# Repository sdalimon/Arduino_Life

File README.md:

# Arduino_Life
A little Arduino compatible LED art project

It consists of a two board stack.  
The lower board has an ATMega328 loaded with the Arduino bootloader.  It also has the row drivers for the LED array.
The upper board is an 8x8 array of LEDs in a standard row/column arrangement.

This was called Arduino Life because I planned to do Game of Life on it, but found a nicer looking pattern that doesn't need to worry about geting stuck.

The software is in the LED_Worm which implements a dot bouncing around the LEDs toggleing the current LED.  It randomly turns to give a less repeatitive pattern.  The software is written using the Arduino IDE.  

To program, use a USB to TTL (or other TTL UART) interface.  Press the reset button after clicking Program in the Arduino IDE (or install the chip in an Arduino Uno and program there).

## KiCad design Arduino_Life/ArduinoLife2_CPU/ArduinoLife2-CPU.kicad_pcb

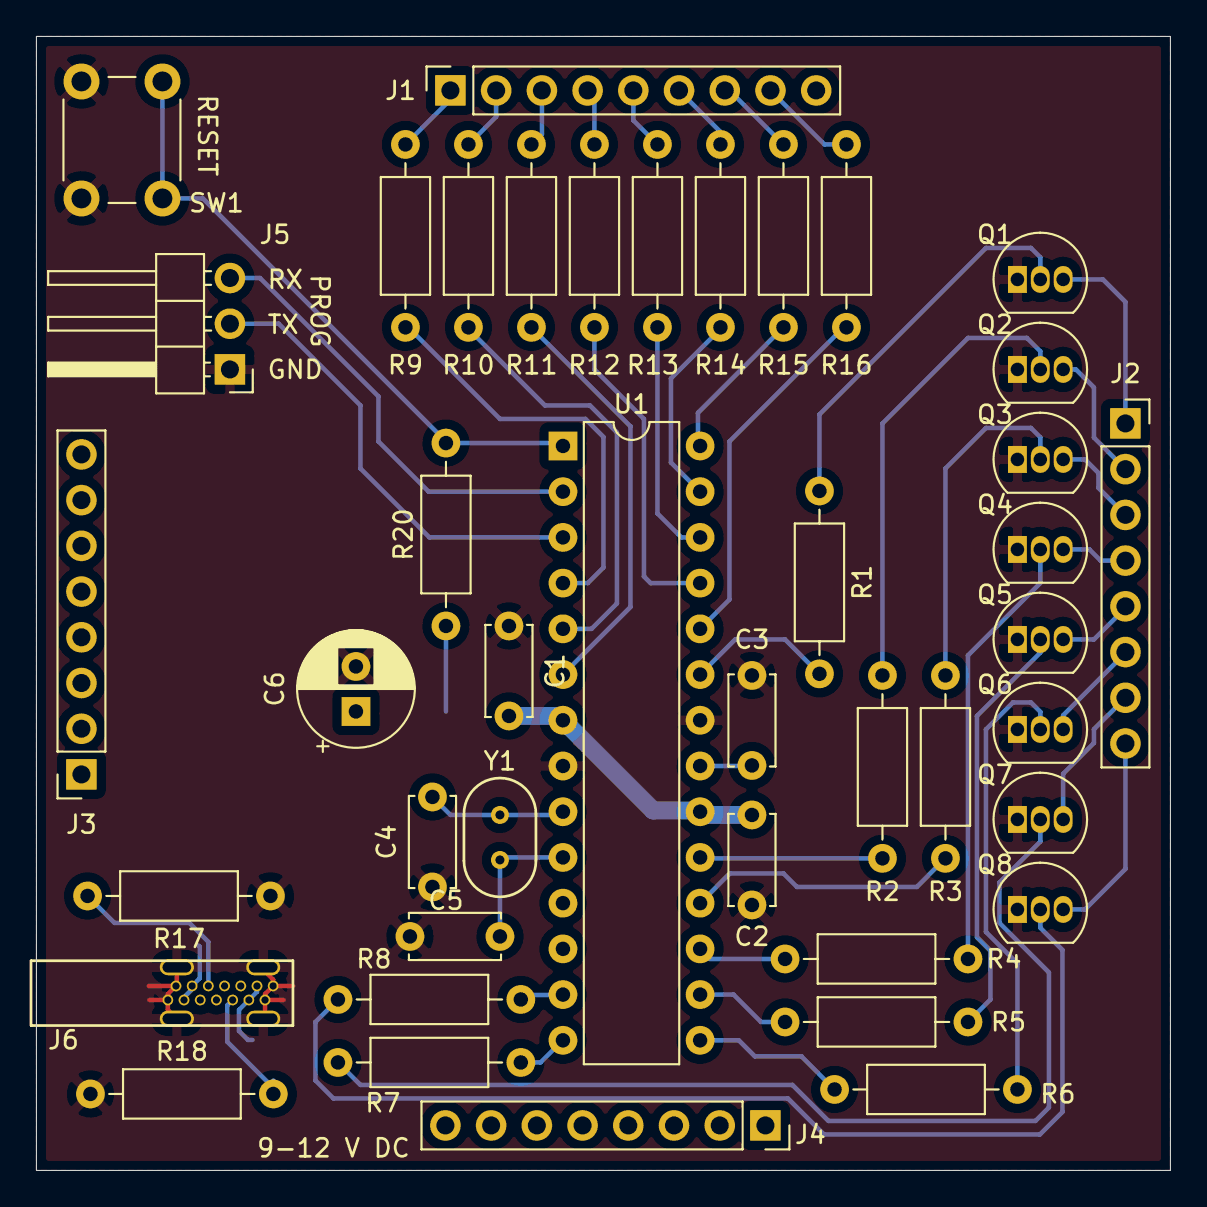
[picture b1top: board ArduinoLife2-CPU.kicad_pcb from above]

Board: 2 copper layers, 63.0 x 63.0 mm, 42 parts (0 on the bottom side), 50 nets.

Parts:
C1, C2, C3: 100n; C_Disc_D5.0mm_W2.5mm_P5.00mm
C4, C5: 22p; C_Disc_D5.0mm_W2.5mm_P5.00mm
C6: 10u; CP_Radial_D6.3mm_P2.50mm
J1: Conn_01x09; PinSocket_1x09_P2.54mm_Vertical
J2, J3, J4: Conn_01x08; PinSocket_1x08_P2.54mm_Vertical
J5: Conn_01x03; PinHeader_1x03_P2.54mm_Horizontal
J6: KUSBX-SL-CS1N14-B
Q1, Q2, Q3, Q4, Q5, Q6, Q7, Q8: 2N3904; TO-92_Inline
R1, R2, R3, R4, R5, R6, R7, R8, R9, R10, R11, R12, R13, R14, R15, R16: 560; R_Axial_DIN0207_L6.3mm_D2.5mm_P10.16mm_Horizontal
R17, R18: 5k1; R_Axial_DIN0207_L6.3mm_D2.5mm_P10.16mm_Horizontal
R20: 10k; R_Axial_DIN0207_L6.3mm_D2.5mm_P10.16mm_Horizontal
SW1: SW_Push; SW_PUSH_6mm
U1: ATmega328P-PU; DIP-28_W7.62mm
Y1: 16M; HC-46X

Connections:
/C0: J1.1, R9.1
/C1: J1.2, R10.1
/C2: J1.3, R11.1
/C3: J1.4, R12.1
/C4: J1.5, R13.1
/C5: J1.6, R14.1
/C6: J1.7, R15.1
/C7: J1.8, R16.1
/CC1: J6.A5, R17.2
/CC2: J6.B5, R18.2
/R0: J2.1, Q1.3
/R1: J2.2, Q2.3
/R2: J2.3, Q3.3
/R3: J2.4, Q4.3
/R4: J2.5, Q5.3
/R5: J2.6, Q6.3
/R6: J2.7, Q7.3
/R7: J2.8, Q8.3
/RX: J5.3, U1.2
/TX: J5.2, U1.3
/UC_C0: R9.2, U1.4
/UC_C1: R10.2, U1.5
/UC_C2: R11.2, U1.6
/UC_C3: R12.2, U1.25
/UC_C4: R13.2, U1.26
/UC_C5: R14.2, U1.27
/UC_C6: R15.2, U1.28
/UC_C7: R16.2, U1.24
/UC_R0: R1.2, U1.23
/UC_R1: R2.2, U1.19
/UC_R2: R3.2, U1.18
/UC_R3: R4.2, U1.17
/UC_R4: R5.2, U1.16
/UC_R5: R6.2, U1.15
/UC_R6: R7.2, U1.14
/UC_R7: R8.2, U1.13
/X1: C4.2, U1.9, Y1.1
/X2: C5.2, U1.10, Y1.2
/~RESET: R20.2, SW1.1, U1.1
GND: C1.1, C2.1, C3.1, C4.1, C5.1, C6.2, J5.1, J6.A1, J6.A12, J6.B1, J6.B12, J6.CASE, Q1.1, Q2.1, Q3.1, Q4.1, Q5.1, Q6.1, Q7.1, Q8.1, R17.1, R18.1, SW1.2, U1.8, U1.22
unnamed: C3.2, U1.21
unnamed: Q1.2, R1.1
unnamed: Q2.2, R2.1
unnamed: Q3.2, R3.1
unnamed: Q4.2, R4.1
unnamed: Q5.2, R5.1
unnamed: Q6.2, R6.1
unnamed: Q7.2, R7.1
unnamed: Q8.2, R8.1
VCC: C1.2, C2.2, C6.1, J6.A4, J6.A9, J6.B4, J6.B9, R20.1, U1.7, U1.20

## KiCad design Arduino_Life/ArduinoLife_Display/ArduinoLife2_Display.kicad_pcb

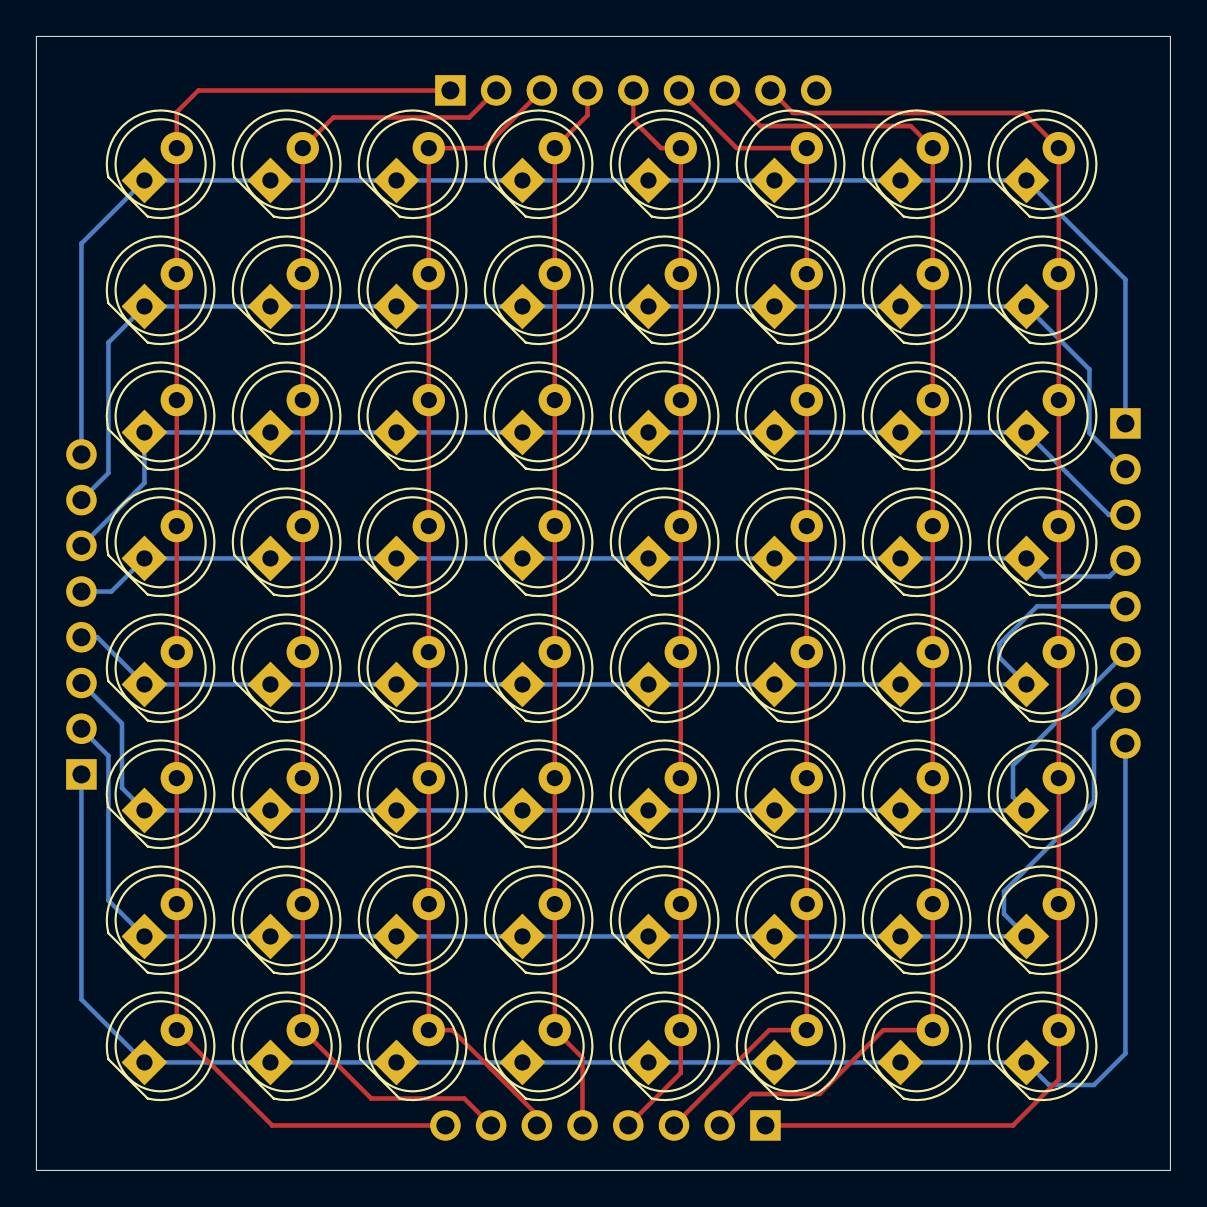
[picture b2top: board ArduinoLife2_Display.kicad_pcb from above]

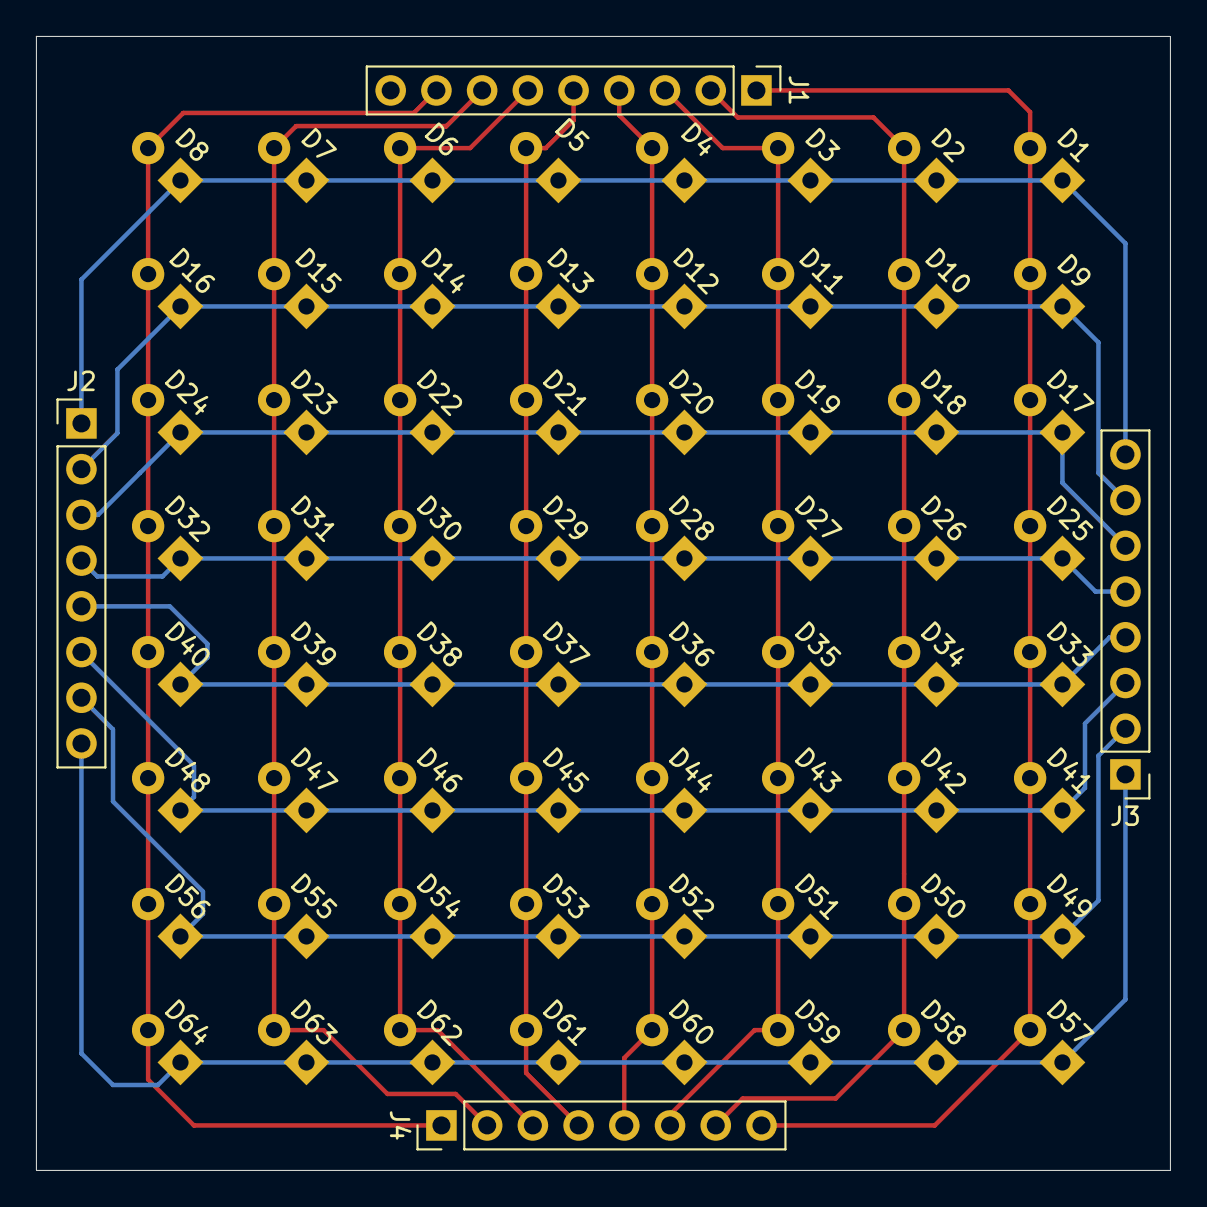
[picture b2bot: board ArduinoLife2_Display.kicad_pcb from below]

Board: 2 copper layers, 63.0 x 63.0 mm, 68 parts (4 on the bottom side), 16 nets.

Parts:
D1, D2, D3, D4, D5, D6, D7, D8, D9, D10, D11, D12, D13, D14, D15, D16, D17, D18, D19, D20, D21, D22, D23, D24, D25, D26, D27, D28, D29, D30, D31, D32, D33, D34, D35, D36, D37, D38, D39, D40, D41, D42, D43, D44, D45, D46, D47, D48, D49, D50, D51, D52, D53, D54, D55, D56, D57, D58, D59, D60, D61, D62, D63, D64: LED; LED_D5.0mm
J1: Conn_01x09; PinHeader_1x09_P2.54mm_Vertical
J2, J3, J4: Conn_01x08; PinHeader_1x08_P2.54mm_Vertical

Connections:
/C0: D1.2, D9.2, D17.2, D25.2, D33.2, D41.2, D49.2, D57.2, J1.1, J4.8
/C1: D2.2, D10.2, D18.2, D26.2, D34.2, D42.2, D50.2, D58.2, J1.2, J4.7
/C2: D3.2, D11.2, D19.2, D27.2, D35.2, D43.2, D51.2, D59.2, J1.3, J4.6
/C3: D4.2, D12.2, D20.2, D28.2, D36.2, D44.2, D52.2, D60.2, J1.4, J4.5
/C4: D5.2, D13.2, D21.2, D29.2, D37.2, D45.2, D53.2, D61.2, J1.5, J4.4
/C5: D6.2, D14.2, D22.2, D30.2, D38.2, D46.2, D54.2, D62.2, J1.6, J4.3
/C6: D7.2, D15.2, D23.2, D31.2, D39.2, D47.2, D55.2, D63.2, J1.7, J4.2
/C7: D8.2, D16.2, D24.2, D32.2, D40.2, D48.2, D56.2, D64.2, J1.8, J4.1
/R0: D1.1, D2.1, D3.1, D4.1, D5.1, D6.1, D7.1, D8.1, J2.1, J3.8
/R1: D9.1, D10.1, D11.1, D12.1, D13.1, D14.1, D15.1, D16.1, J2.2, J3.7
/R2: D17.1, D18.1, D19.1, D20.1, D21.1, D22.1, D23.1, D24.1, J2.3, J3.6
/R3: D25.1, D26.1, D27.1, D28.1, D29.1, D30.1, D31.1, D32.1, J2.4, J3.5
/R4: D33.1, D34.1, D35.1, D36.1, D37.1, D38.1, D39.1, D40.1, J2.5, J3.4
/R5: D41.1, D42.1, D43.1, D44.1, D45.1, D46.1, D47.1, D48.1, J2.6, J3.3
/R6: D49.1, D50.1, D51.1, D52.1, D53.1, D54.1, D55.1, D56.1, J2.7, J3.2
/R7: D57.1, D58.1, D59.1, D60.1, D61.1, D62.1, D63.1, D64.1, J2.8, J3.1

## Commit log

2021-02-15 Add files via upload
    First Upload
2021-02-15 Update README.md
    Update Readme
2021-02-15 Add files via upload
    Add software
